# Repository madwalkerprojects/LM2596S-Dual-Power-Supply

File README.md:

# LM2596S-Dual-Power-Supply
LM2596S based dual power supply. 5V and 3.3V

Schematic:

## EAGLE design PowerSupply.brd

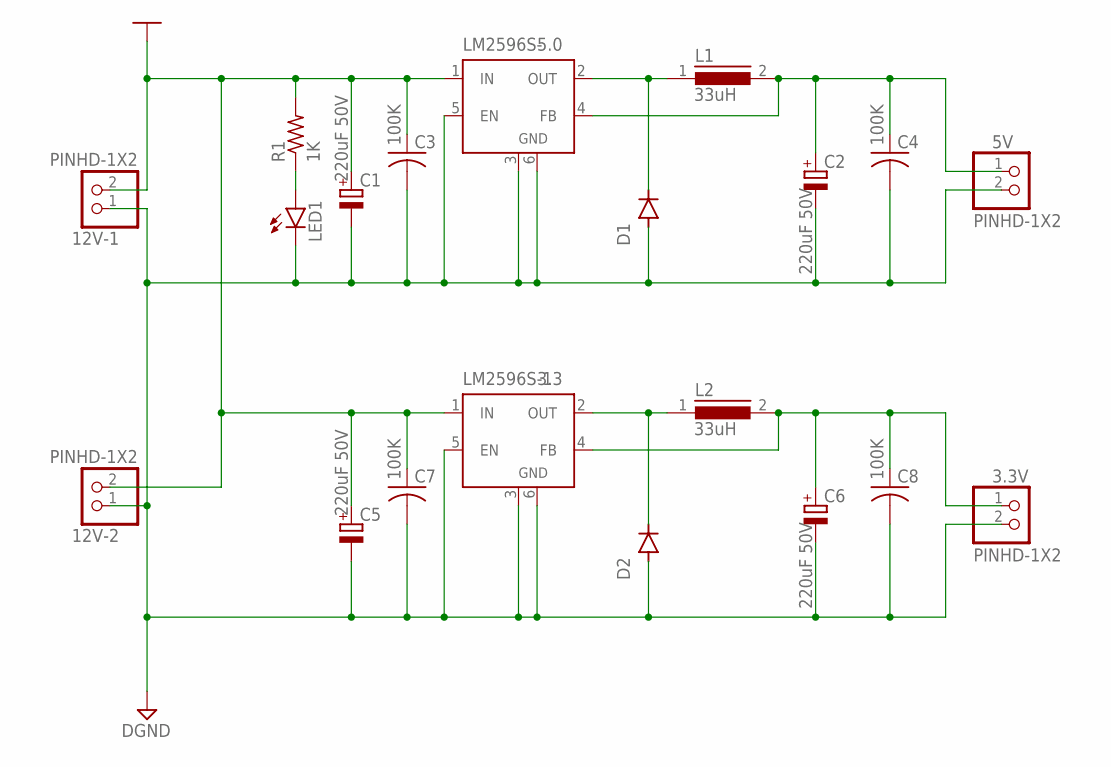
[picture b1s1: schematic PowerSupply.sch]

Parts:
3.3V, 5V, 12V-1, 12V-2: PINHD-1X2; 1X02
C1, C2, C5, C6: 220uF 50V; CAPAE1030X1050N
C3, C4, C7, C8: 100K; CAPC3216X135
D1, D2: DIODE-DO214AA; DO214AA
L1, L2: 33uH; SRR1210
LED1: LEDCHIPLED_1206; CHIPLED_1206
LM2596S-: 5.0; TO263-5
LM2596S-1: 3.3; TO263-5
R1: 1K; R1206

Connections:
DGND: 3.3V.2, 5V.2, 12V-1.1, 12V-2.1, C1.2 (-), C2.2 (-), C3.2, C4.2, C5.2 (-), C6.2 (-), C7.2, C8.2, D1.A, D2.A, LED1.C, LM2596S-.3 (GND), LM2596S-.5 (EN), LM2596S-.6 (GND), LM2596S-1.3 (GND), LM2596S-1.5 (EN), LM2596S-1.6 (GND)
unnamed: LED1.A, R1.1
unnamed: D1.C, L1.1, LM2596S-.2 (OUT)
unnamed: 5V.1, C2.1 (+), C4.1, L1.2, LM2596S-.4 (FB)
unnamed: D2.C, L2.1, LM2596S-1.2 (OUT)
unnamed: 3.3V.1, C6.1 (+), C8.1, L2.2, LM2596S-1.4 (FB)
VCC: 12V-1.2, 12V-2.2, C1.1 (+), C3.1, C5.1 (+), C7.1, LM2596S-.1 (IN), LM2596S-1.1 (IN), R1.2

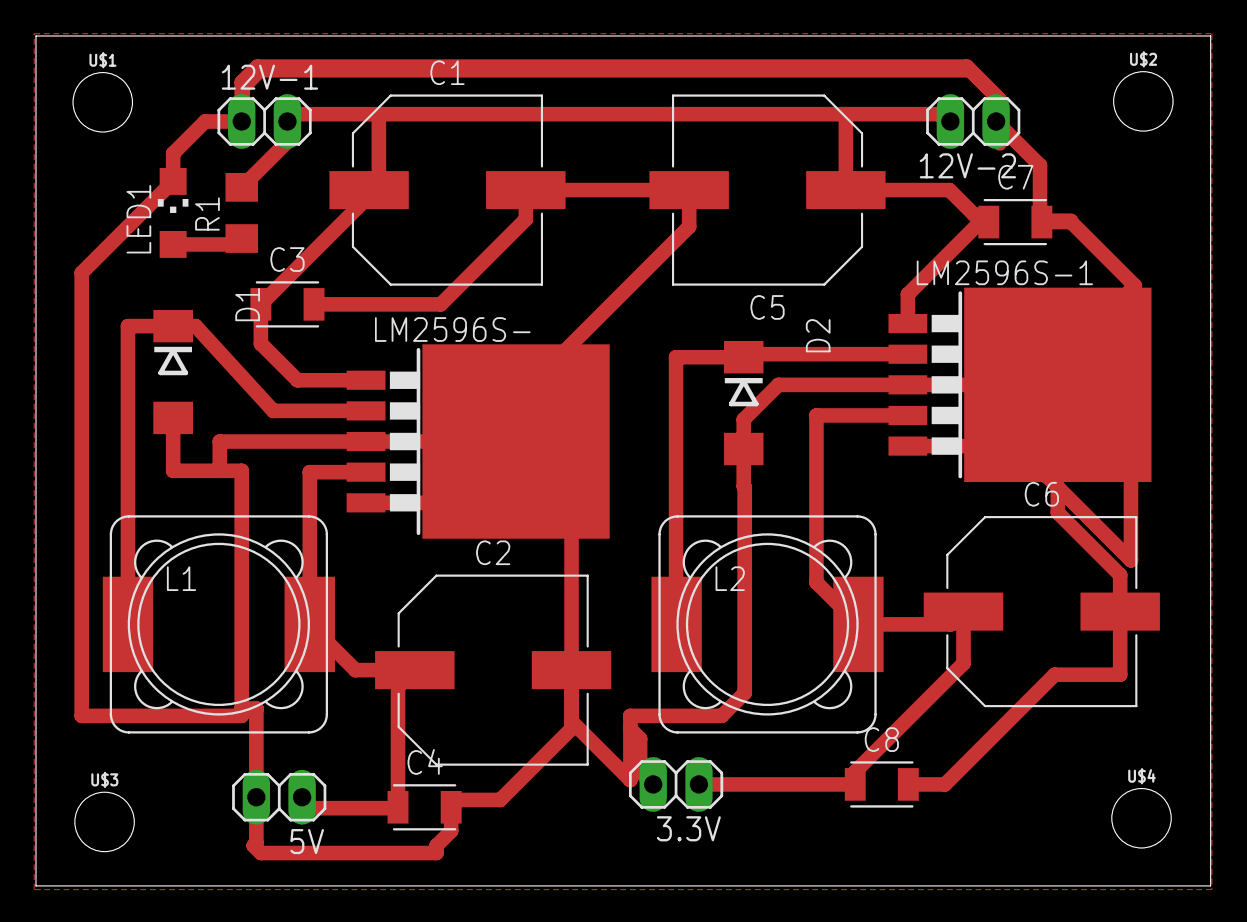
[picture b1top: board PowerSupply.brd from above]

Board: 2 copper layers, 65.3 x 47.2 mm, 24 parts (0 on the bottom side), 7 nets.

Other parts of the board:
U$1, U$2, U$3, U$4: STAND-OFF

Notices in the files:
parts and their libraries:
SparkFun-Hardware: Licensing: Creative Commons ShareAlike 4.0 International - https://creativecommons.org/licenses/by-sa/4.0
